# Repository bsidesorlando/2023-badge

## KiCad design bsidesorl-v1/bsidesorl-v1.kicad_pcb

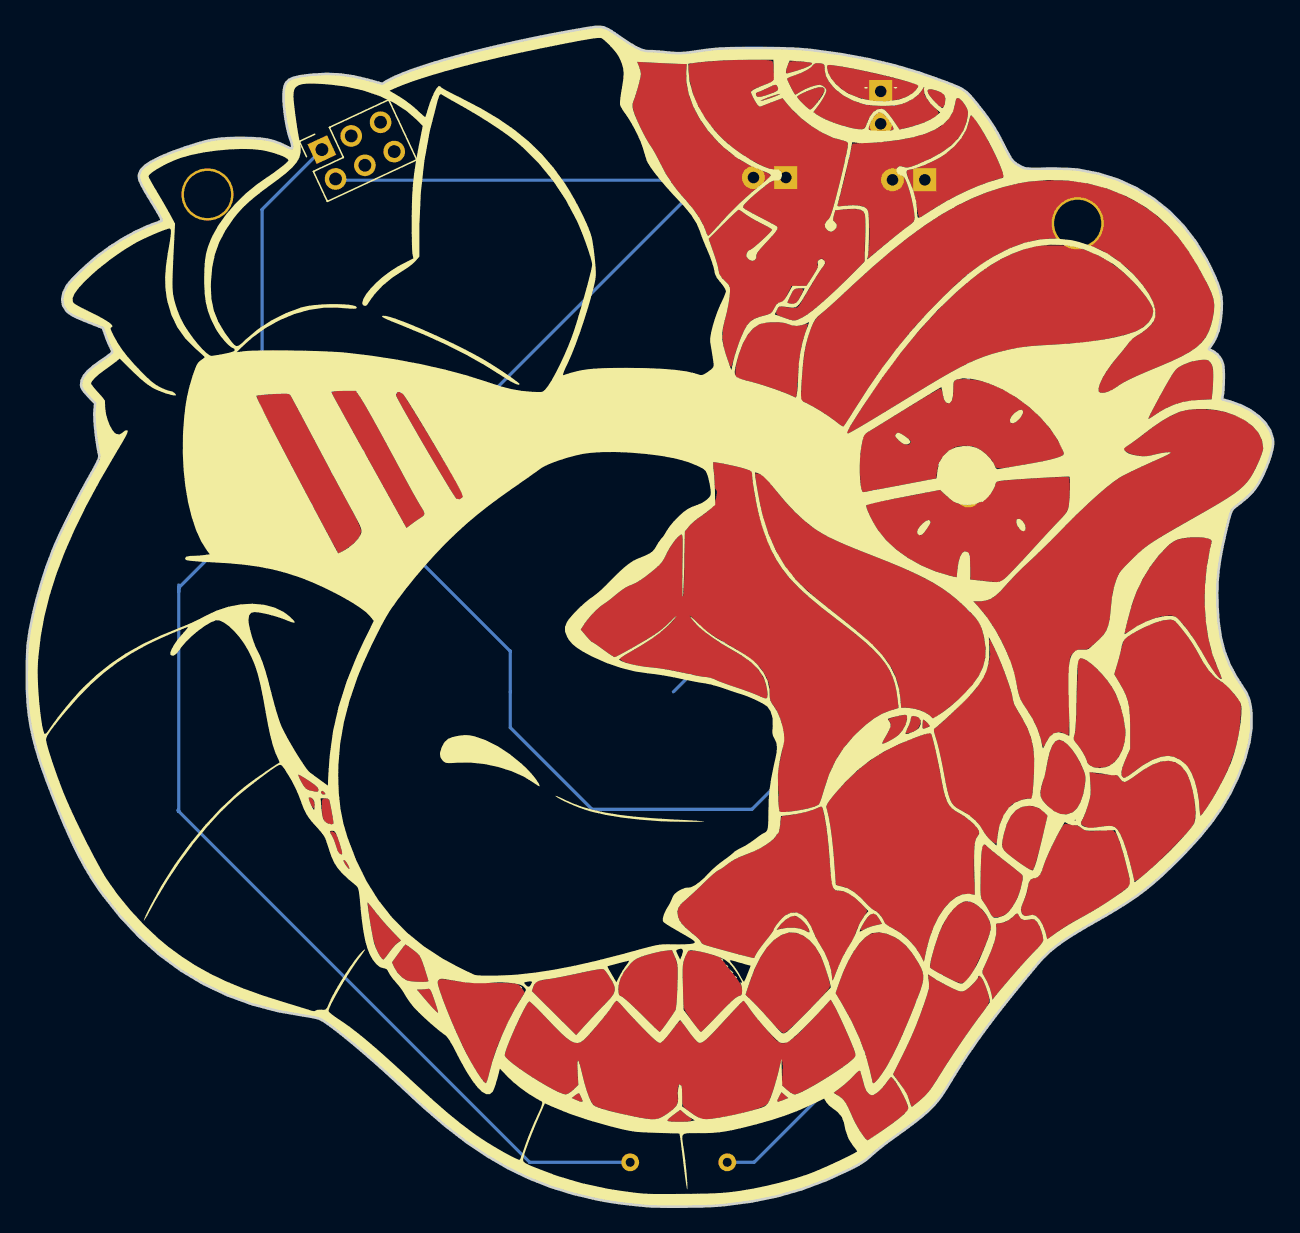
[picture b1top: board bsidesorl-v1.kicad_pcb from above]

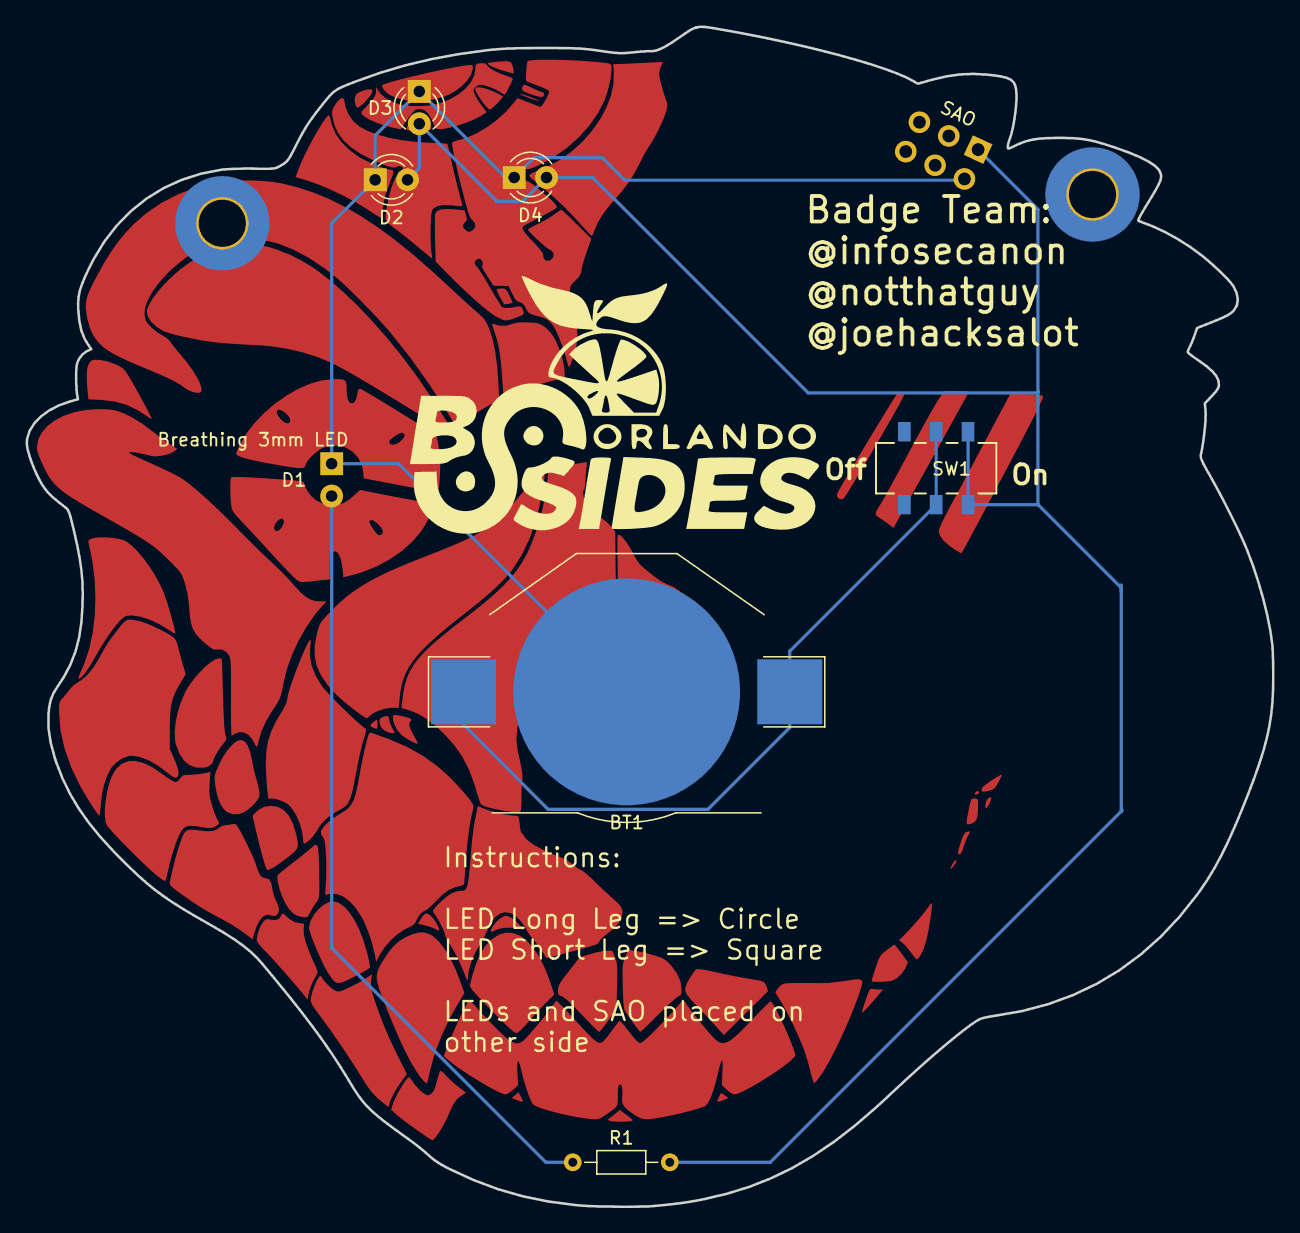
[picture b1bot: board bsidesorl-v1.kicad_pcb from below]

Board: 2 copper layers, 97.8 x 92.6 mm, 8 parts (3 on the bottom side), 4 nets.

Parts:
BT1: Battery_Cell; BatteryHolder_Keystone_3002_1x2032
D1: Breathing 3mm LED; LED_D3.0mm_IRBlack
D2, D3, D4: Fast Blink 3mm LED; LED_D3.0mm_IRBlack
R1: 56 Ohm; R_Axial_DIN0204_L3.6mm_D1.6mm_P7.62mm_Horizontal
SAO: Conn_02x03_Top_Bottom; PinSocket_2x03_P2.54mm_Vertical
SW1: MST22D18G2 125; SOIC6_SW6_MST22D18G2_SHN

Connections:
unnamed: BT1.1 (+), SW1.2, SW1.5
unnamed: BT1.2 (-), D1.1 (K), D2.1 (K), D3.1 (K), D4.1 (K), SAO.2
unnamed: D1.2 (A), R1.1
unnamed: D2.2 (A), D3.2 (A), D4.2 (A), R1.2, SAO.1, SW1.1, SW1.6

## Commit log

2023-09-04 introduction
2023-09-07 introduced additional sao
2023-09-11 added 561
